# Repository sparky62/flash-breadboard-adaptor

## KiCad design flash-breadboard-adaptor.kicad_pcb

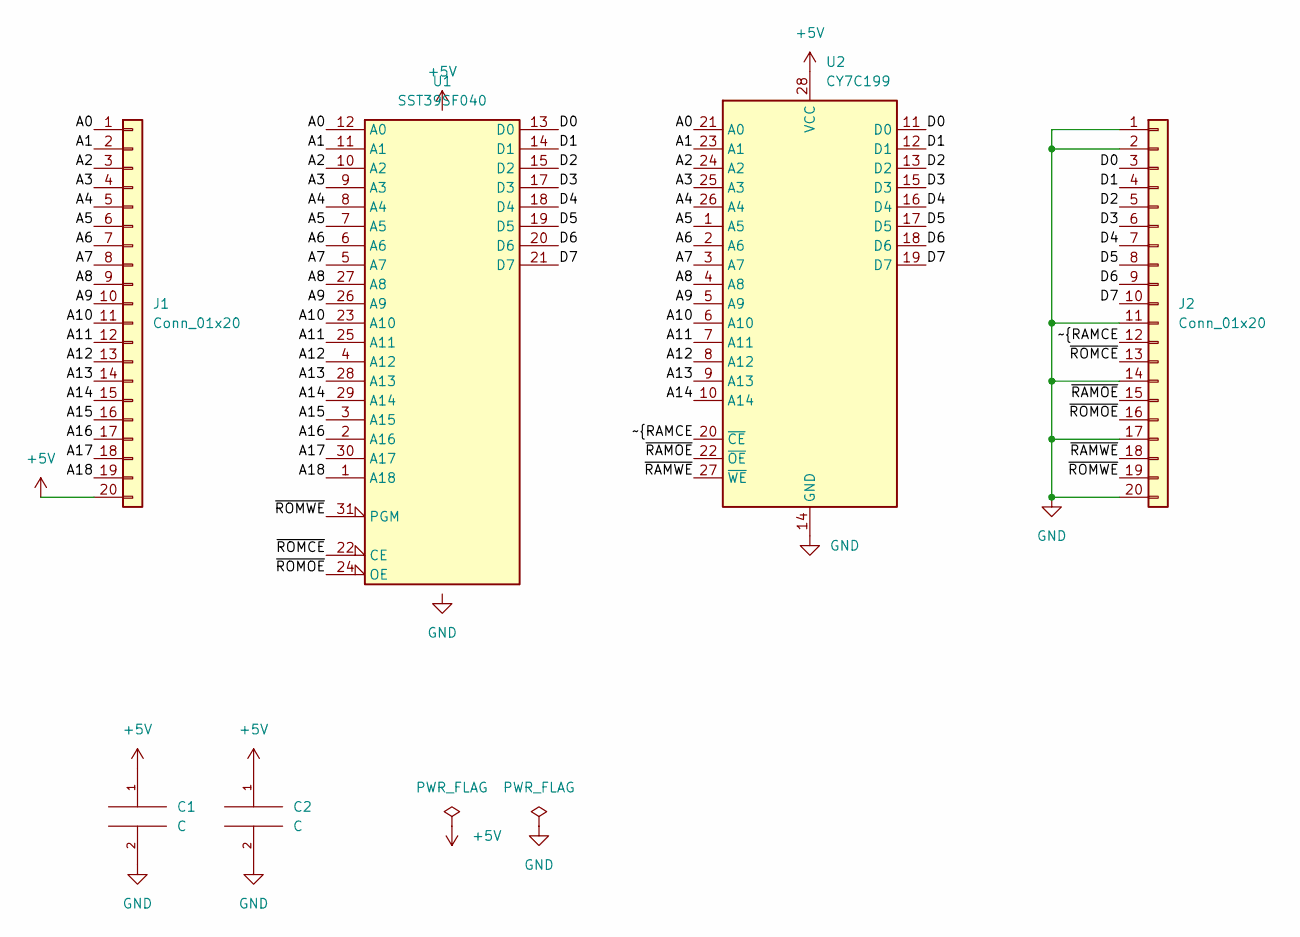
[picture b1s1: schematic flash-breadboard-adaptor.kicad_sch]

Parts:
C1, C2: C; C_Disc_D4.3mm_W1.9mm_P5.00mm
J1, J2: Conn_01x20; PinHeader_1x20_P2.54mm_Vertical
U1: SST39SF040; DIP_Socket-32_W11.9_W12.7_W15.24_W17.78_W18.5_3M_232-1285-0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
U2: CY7C199; DIP-28_W7.62mm_Socket

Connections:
+5V: C1.1, C2.1, J1.20, U1.32 (VCC), U2.28 (VCC)
/A0: J1.1, U1.12 (A0), U2.21 (A0)
/A1: J1.2, U1.11 (A1), U2.23 (A1)
/A2: J1.3, U1.10 (A2), U2.24 (A2)
/A3: J1.4, U1.9 (A3), U2.25 (A3)
/A4: J1.5, U1.8 (A4), U2.26 (A4)
/A5: J1.6, U1.7 (A5), U2.1 (A5)
/A6: J1.7, U1.6 (A6), U2.2 (A6)
/A7: J1.8, U1.5 (A7), U2.3 (A7)
/A8: J1.9, U1.27 (A8), U2.4 (A8)
/A9: J1.10, U1.26 (A9), U2.5 (A9)
/A10: J1.11, U1.23 (A10), U2.6 (A10)
/A11: J1.12, U1.25 (A11), U2.7 (A11)
/A12: J1.13, U1.4 (A12), U2.8 (A12)
/A13: J1.14, U1.28 (A13), U2.9 (A13)
/A14: J1.15, U1.29 (A14), U2.10 (A14)
/A15: J1.16, U1.3 (A15)
/A16: J1.17, U1.2 (A16)
/A17: J1.18, U1.30 (A17)
/A18: J1.19, U1.1 (A18)
/D0: J2.3, U1.13 (D0), U2.11 (D0)
/D1: J2.4, U1.14 (D1), U2.12 (D1)
/D2: J2.5, U1.15 (D2), U2.13 (D2)
/D3: J2.6, U1.17 (D3), U2.15 (D3)
/D4: J2.7, U1.18 (D4), U2.16 (D4)
/D5: J2.8, U1.19 (D5), U2.17 (D5)
/D6: J2.9, U1.20 (D6), U2.18 (D6)
/D7: J2.10, U1.21 (D7), U2.19 (D7)
/~RAMCE: J2.12, U2.20 (~CE)
/~RAMOE: J2.15, U2.22 (~OE)
/~RAMWE: J2.18, U2.27 (~WE)
/~ROMCE: J2.13, U1.22 (CE)
/~ROMOE: J2.16, U1.24 (OE)
/~ROMWE: J2.19, U1.31 (PGM)
GND: C1.2, C2.2, J2.1, J2.2, J2.11, J2.14, J2.17, J2.20, U1.16 (GND), U2.14 (GND)

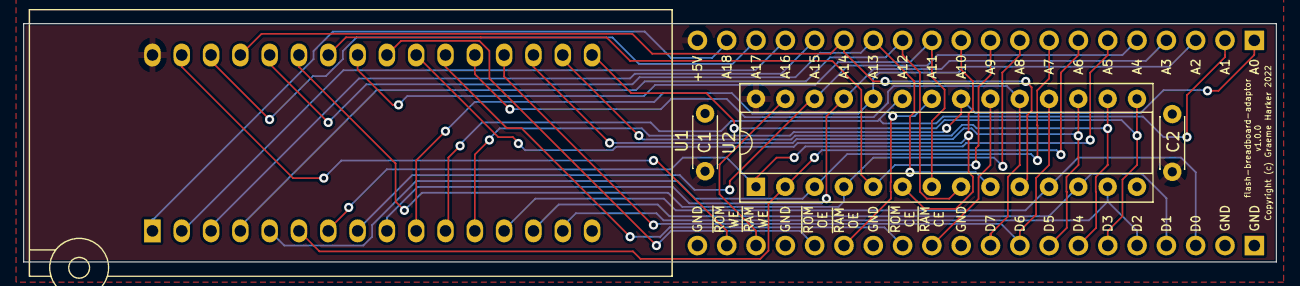
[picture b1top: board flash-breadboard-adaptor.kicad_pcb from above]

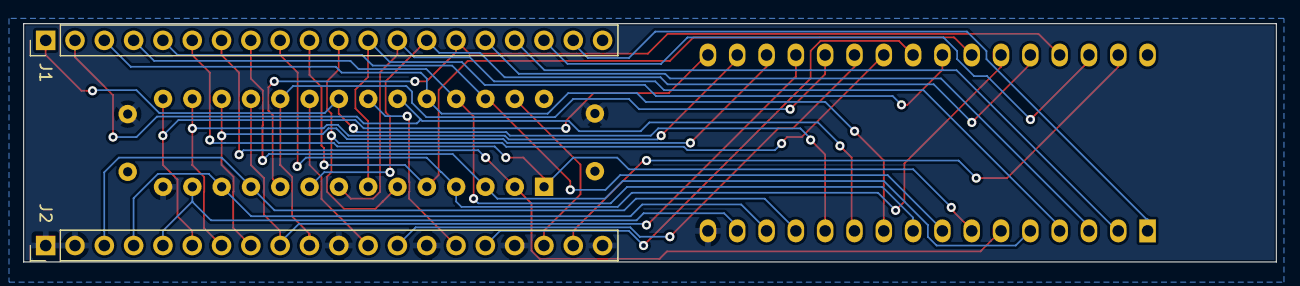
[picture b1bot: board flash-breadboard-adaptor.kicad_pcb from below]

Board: 2 copper layers, 108.6 x 20.7 mm, 6 parts (2 on the bottom side), 35 nets.

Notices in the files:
flash-breadboard-adaptor.kicad_pcb:
Copyright (c) Graeme Harker 2022
